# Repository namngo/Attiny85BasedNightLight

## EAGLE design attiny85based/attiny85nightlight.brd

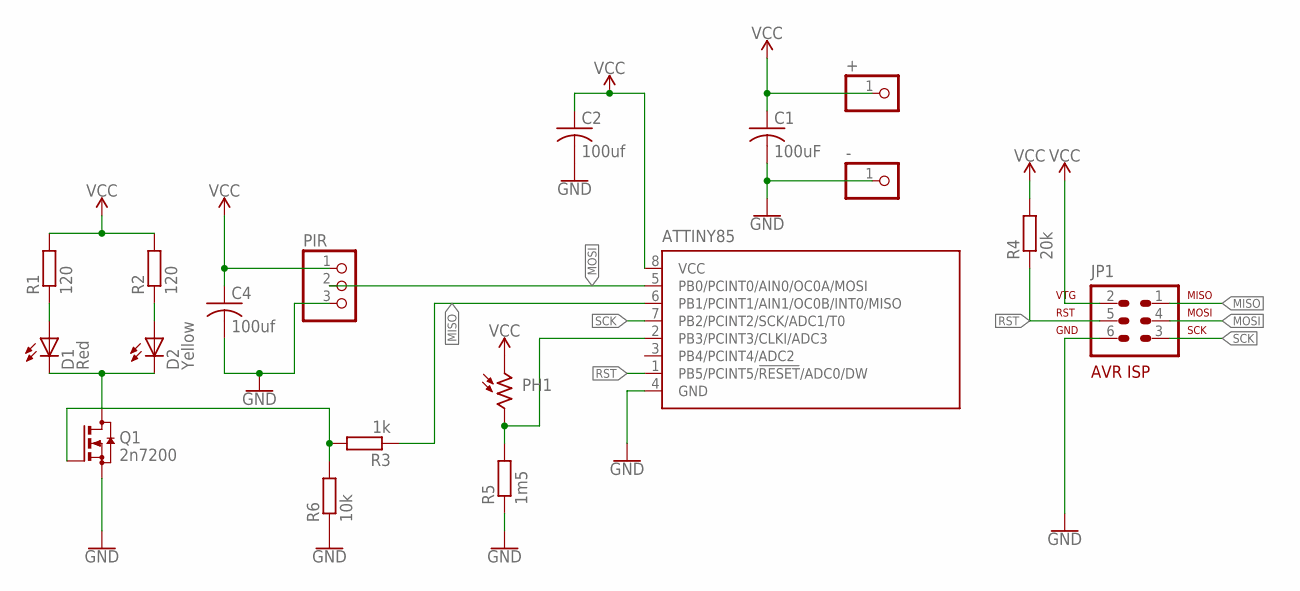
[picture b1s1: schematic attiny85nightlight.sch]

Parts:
+: PINHD-1X1; 1X01
-: PINHD-1X1; 1X01
ATTINY85: TINY13-20SU; 8S2
C1: 100uF; C0805
C2, C4: 100uf; C0805
D1: Red; LED5MM
D2: Yellow; LED5MM
JP1: AVR-ISP-6
PH1: A1050_09; T0-46-A10XX
PIR: PINHD-1X3; 1X03
Q1: 2n7200; SOT23
R1, R2: 120; R0805
R3: 1k; R0805
R4: 20k; R0805
R5: 1m5; R0805
R6: 10k; R0805

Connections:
GND: -.1, ATTINY85.4 (GND), C1.2, C2.2, C4.2, JP1.6, PIR.3, Q1.2 (S), R5.1, R6.1
MISO: ATTINY85.6 (PB1/PCINT1/AIN1/OC0B/INT0/MISO), JP1.1, R3.1
MOSI: ATTINY85.5 (PB0/PCINT0/AIN0/OC0A/MOSI), JP1.4, PIR.2
unnamed: D1.K (C), D2.K (C), Q1.3 (D)
unnamed: ATTINY85.2 (PB3/PCINT3/CLKI/ADC3), PH1.2, R5.2
unnamed: D1.A, R1.1
unnamed: D2.A, R2.1
unnamed: Q1.1 (G), R3.2, R6.2
RST: ATTINY85.1 (PB5/PCINT5/!RESET!/ADC0/DW), JP1.5, R4.1
SCK: ATTINY85.7 (PB2/PCINT2/SCK/ADC1/T0), JP1.3
VCC: +.1, ATTINY85.8 (VCC), C1.1, C2.1, C4.1, JP1.2, PH1.1, PIR.1, R1.2, R2.2, R4.2

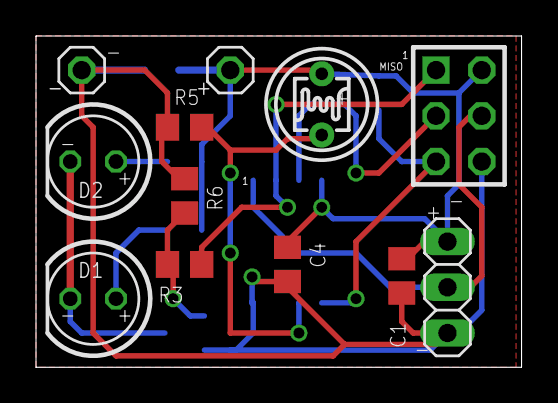
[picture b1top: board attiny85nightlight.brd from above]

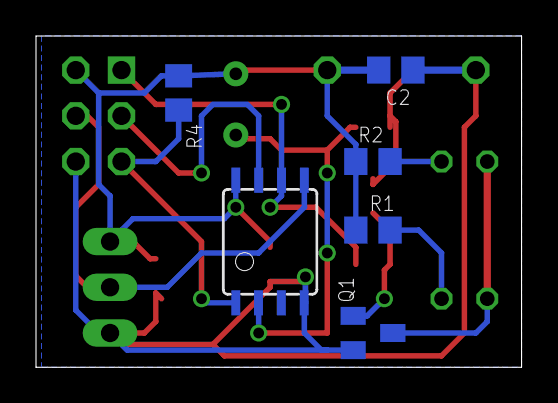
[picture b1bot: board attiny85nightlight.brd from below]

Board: 2 copper layers, 27.0 x 18.4 mm, 18 parts (6 on the bottom side), 11 nets.

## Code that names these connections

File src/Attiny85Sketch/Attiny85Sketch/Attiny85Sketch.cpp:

#include "arduino.h"
#include <avr/sleep.h>    // Sleep Modes
#include <avr/power.h>    // Power management
#include <avr/wdt.h>      // Watchdog timer
#include <SoftwareSerial.h>

/*
 * Attiny85Sketch.ino
 *
 * Created: 5/29/2017 10:52:34 PM
 * Author: nam
 */ 

#define INTERNAL2V56_NO_CAP (6)


#define LED_PORT PB1
#define LDR_PORT PB3
#define PIR_PORT PB0

#define TxPin PB2
#define RxPin PB4

#define Sleep_Time_Second 2

#define Light_Dark_Value 650
#define Light_On_In_Second 120 / Sleep_Time_Second
#define Light_Off_In_Second 30 / Sleep_Time_Second


SoftwareSerial serial(RxPin, TxPin);

// this variable represent the state of the led
// 0 - led is off
// > 0 the number of second the led has been on
volatile int led_state = 0;

void setup()
{
    analogReference(DEFAULT);
      /* add setup code here, setup code runs once when the processor starts */
    pinMode(LED_PORT, OUTPUT);
    pinMode(LDR_PORT, INPUT);
    pinMode(PIR_PORT, INPUT);
    
    serial.begin(9600);
}

void check_light()
{
    cli();
    
    if (led_state == 0)
    {
        int light_value = analogRead(LDR_PORT);
        serial.print("light value =");
        serial.println(light_value);
        
        if (light_value < Light_Dark_Value)
        {
            int has_movement = digitalRead(PIR_PORT);
            serial.println(has_movement);
            if (has_movement == 1)
            {
                serial.print("movement! ");
                serial.println(light_value);
                led_state = 1;
                digitalWrite(LED_PORT, HIGH);
            }
        }
    }
    else
    {
        serial.print("led state=");
        serial.println(led_state);
        led_state ++;
        if (led_state == Light_On_In_Second)
        {
            digitalWrite(LED_PORT, LOW);
            serial.println("off light");
        }
        else if (led_state == Light_On_In_Second + Light_Off_In_Second)
        {
            led_state = 0;
            serial.println("reset");
        }
    }
    
    sei();
}

void resetWatchdog ()
{
    // clear various "reset" flags
    MCUSR = 0;
    // allow changes, disable reset, clear existing interrupt
    WDTCR = (1 << WDCE) | (1 << WDE) | (1 << WDIF);
    // set interrupt mode and an interval (WDE must be changed from 1 to 0 here)
    WDTCR = (1 << WDIE) | (1 << WDP2) | (1 << WDP1) | (1 << WDP0);    // set WDIE, and 1 seconds delay
    // pat the dog
    wdt_reset();
}  // end of resetWatchdog

void go_to_sleep()
{
    set_sleep_mode(SLEEP_MODE_PWR_DOWN);
    power_all_disable();
    resetWatchdog();
    sleep_enable();
    sei();
    sleep_cpu();
    sleep_disable();
    power_all_enable();
}

ISR( WDT_vect ) {
    /* dummy */
    wdt_disable();
}

void loop()
{
    check_light();
    go_to_sleep();
}

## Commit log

2017-03-16 first
2017-03-17 generate board
2017-03-17 end of day
2017-03-18 complete 1
2017-03-19 foo bar
2017-04-23 remove code
2017-04-23 add code
2017-04-25 nail down adc
2017-06-01 new and simplier
2017-06-10 done
2017-06-10 remove hex files

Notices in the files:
parts and their libraries:
SparkFun-PowerSymbols: Licensing: Creative Commons ShareAlike 4.0 International - https://creativecommons.org/licenses/by-sa/4.0
